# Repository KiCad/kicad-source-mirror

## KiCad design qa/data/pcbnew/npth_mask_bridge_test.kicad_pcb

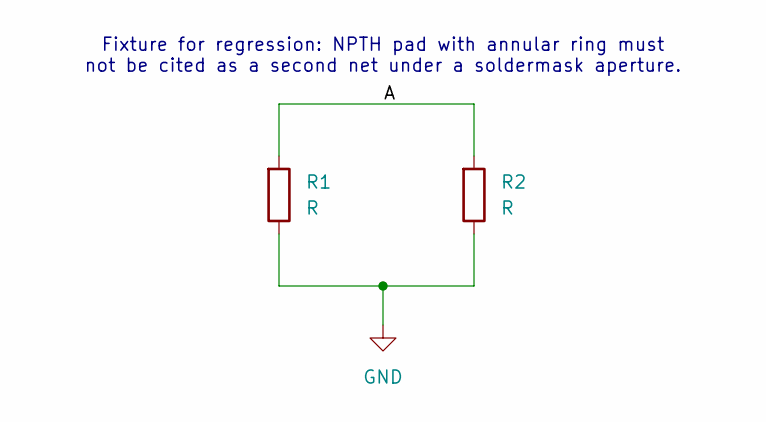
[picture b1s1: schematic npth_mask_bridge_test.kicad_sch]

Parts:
R1, R2: R; R_0805_2012Metric

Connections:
/A: R1.1, R2.1
GND: R1.2, R2.2

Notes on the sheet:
Fixture for regression: NPTH pad with annular ring must not be cited as a second net under a soldermask aperture.

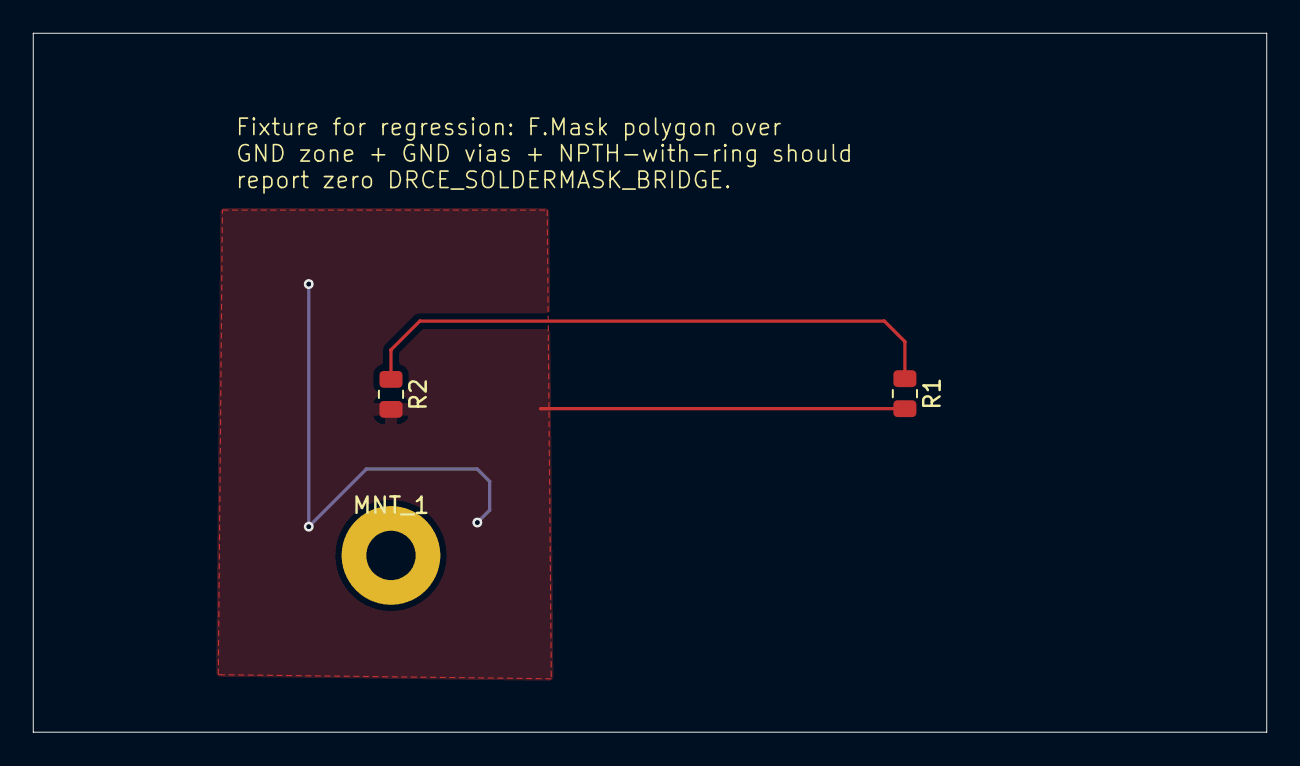
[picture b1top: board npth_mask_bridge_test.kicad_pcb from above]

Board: 2 copper layers, 75.0 x 42.5 mm, 3 parts (0 on the bottom side), 2 nets.

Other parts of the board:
MNT_1: MountingHole_2.1mm
